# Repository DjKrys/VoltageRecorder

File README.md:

# VoltageRecorder
Celem projektu było zaprojektowanie, montaż i uruchomienie wielokanałowego rejestratora danych do precyzyjnego pomiaru napięcia(The aim of the project was to design, assemble and launch Multi-channel data logger for precise voltage measurement). My engineer's thesis.

# Cel i zakres pracy
Celem pracy jest zaprojektowanie oraz budowa rejestratora do precyzyjnego pomiaru napięcia o zasilaniu bateryjnym. Urządzenie to musi pozwolić na szybką archiwizację danych oraz zapisanie ich w postaci cyfrowej na nieulotną pamięć FLASH. Zbieranie i rejestracja danych na nośnik pamięci o odpowiedniej pojemności pozwala ponadto na prowadzenie wielogodzinnych pomiarów. Aby osiągnąć cel został wykonany schemat elektryczny urządzenia, a następnie na jego podstawie wykonana płytka PCB. Drugim krokiem będzie stworzenie algorytmu w języku C, w celu obsługi podzespołów oraz zarządzania danymi. Zostanie stworzony prosty interfejs użytkownika umożliwiający ustawienie parametrów archiwizacji (ilość próbek na sekundę, zakres pomiarowy), prezentację wyników oraz kalibracje urządzenia.
Ostatnim krokiem była doświadczalna weryfikacja działania układu oraz próba określenia uzyskanych parametrów.

# Założenia
* Urządzenie zasilane z akumulatorka (z pełną jego obsługą, czyli ładowarką + monitoringiem stanu naładowania)
* Pomiary napięcia w ośmiu kanałach analogowych
* Zapis pomiarów do pliku na kartę SD wraz z interwałami czasowymi
* Wyświetlanie informacji na wyświetlaczu
* Projekt płytki PCB oraz montaż 
* Testowe oprogramowanie

# Weryfikacja działania
https://drive.google.com/file/d/1y4KWzrLdbeENvkOfH9YcUIEn7dakh6ji/view?usp=sharing

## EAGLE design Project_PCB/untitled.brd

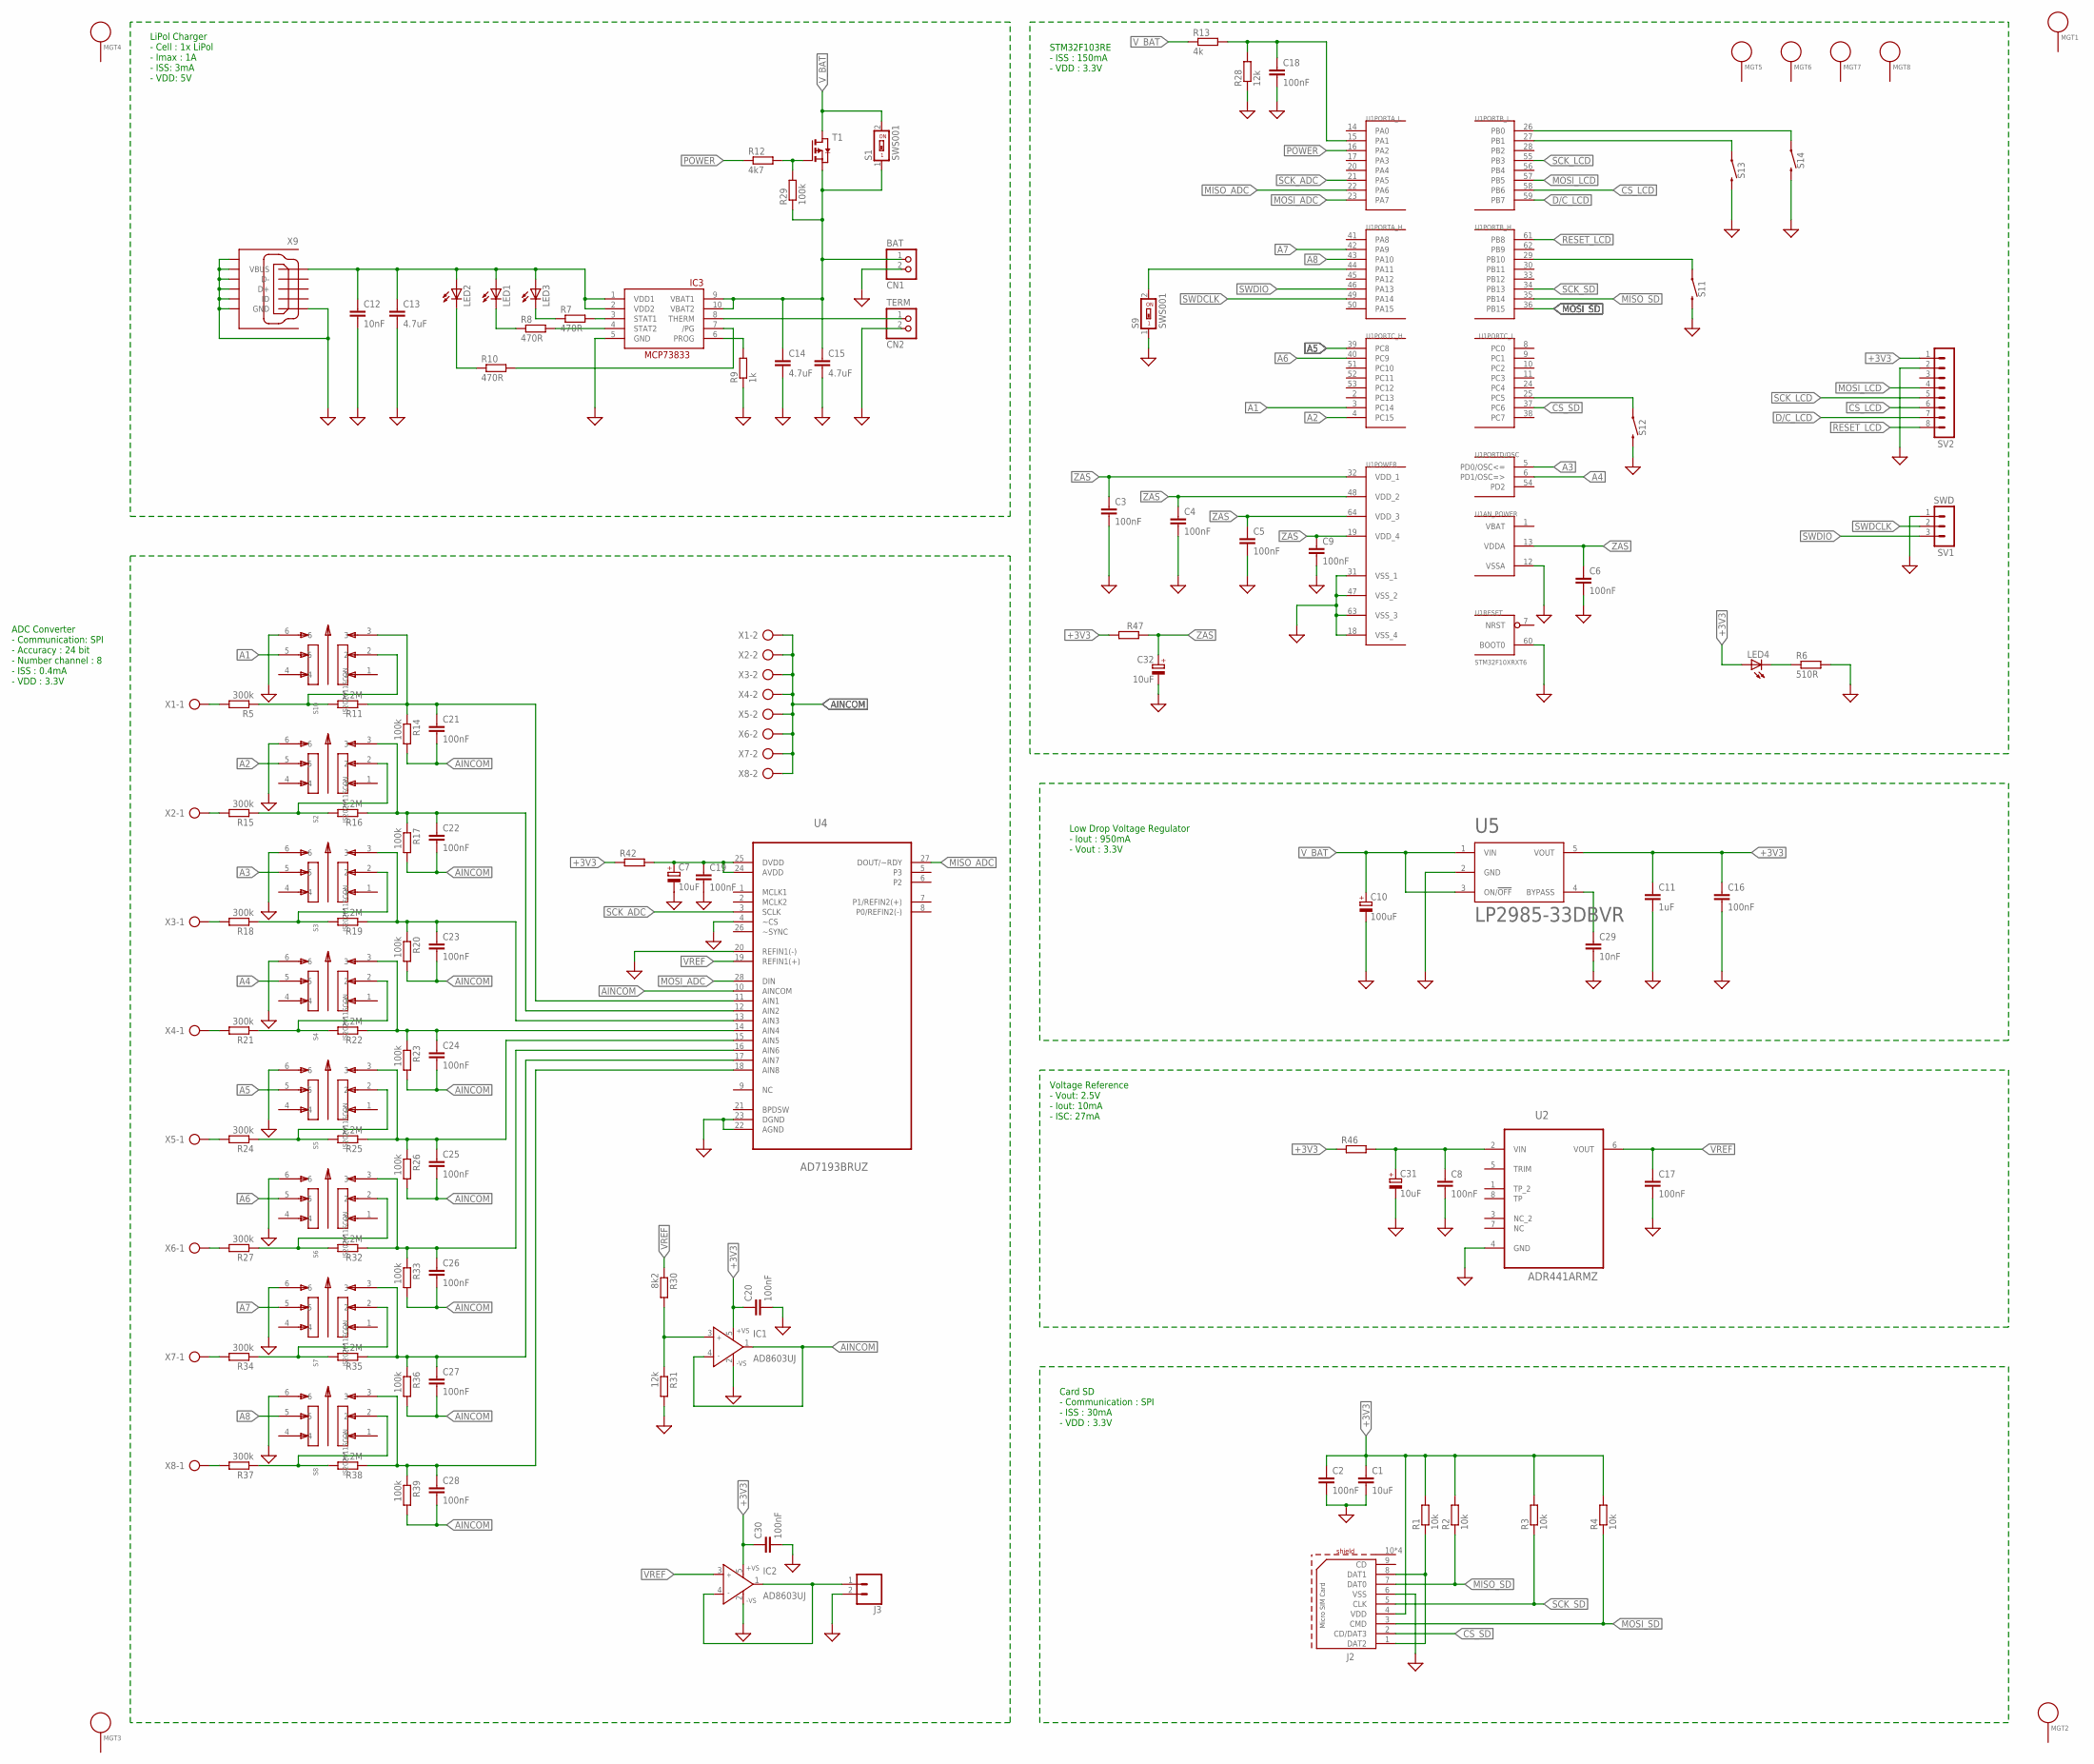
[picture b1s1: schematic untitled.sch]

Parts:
C1: 10uF; C0805
C2, C3, C4, C5, C6, C8, C9, C16, C17, C18, C19, C20, C21, C22, C23, C24, C25, C26, C27, C28, C30: 100nF; C0805
C7, C31, C32: 10uF; SMC_B
C10: 100uF; SMC_B
C11: 1uF; C0805
C12, C29: 10nF; C0805
C13, C14, C15: 4.7uF; C0805
CN1: BAT; JST-PH-2-THM-RA
CN2: TERM; JST-PH-2-THM-RA
IC1, IC2: AD8603UJ; SOT23-5
IC3: MCP73833-UN; MSOP10
J2: 693071020811
J3: CONN_02PTH3; 1X02_LONGPADS
LED1, LED2, LED3, LED4: LEDCHIP-LED0805; CHIP-LED0805
MGT1, MGT2, MGT3, MGT4, MGT5, MGT6, MGT7, MGT8: MOUNTING_HOLE; BEAGLEBONEBLACK_MOUNTING_HOLE
R1, R2, R3, R4: 10k; R0805
R5, R15, R18, R21, R24, R27, R34, R37: 300k; R0805
R6: 510R; R0805
R7, R8, R10: 470R; R0805
R9: 1k; R0805
R11, R16, R19, R22, R25, R32, R35, R38: 1.2M; R0805
R12: 4k7; R0805
R13: 4k; R0805
R14, R17, R20, R23, R26, R29, R33, R36, R39: 100k; R0805
R28, R31: 12k; R0805
R30: 8k2; R0805
R42, R46, R47: R-EU_R1206; R1206
S1, S9: SWS001; SMS-001
S2, S3, S4, S5, S6, S7, S8, S10: JS202011SCQN; SW_JS202011SCQN
S11, S12, S13, S14: MOMENTARY-SWITCH-SPST-SMD-6.2MM-TALL; TACTILE_SWITCH_SMD_6.2MM_TALL
SV1: SWD; MA03-1
SV2: MA08-1
T1: PMOSSOT223; SOT223
U1: STM32F10XRXT6; TQFP64
U2: ADR441ARMZ; SOP65P490X110-8N
U4: AD7193BRUZ; SOP65P640X120-28N
U5: LP2985-33DBVR; SOT-23-5
X1, X2, X3, X4, X5, X6, X7, X8: AK300/2
X9: GHI-CONNECTORS_10118192-0001LF; GHI-CONNECTORS_10118192-0001LF(MICRO-USB-B-AMPHENOL-FCI)

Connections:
+3V3: C1.1, C2.1, C11.1, C16.1, C20.1, C30.1, IC1.5 (+VS), IC2.5 (+VS), J2.4 (VDD), LED4.A, R1.2, R2.2, R3.2, R4.2, R42.1, R46.1, R47.2, SV2.1, U5.5 (VOUT)
A1: S10.5, U1.3 (PC14)
A2: S2.5, U1.4 (PC15)
A3: S3.5, U1.5 (PD0/OSC<=)
A4: S4.5, U1.6 (PD1/OSC=>)
A5: S5.5, U1.39 (PC8)
A6: S6.5, U1.40 (PC9)
A7: S7.5, U1.42 (PA9)
A8: S8.5, U1.43 (PA10)
AINCOM: C21.2, C22.2, C23.2, C24.2, C25.2, C26.2, C27.2, C28.2, IC1.1 (OUT), IC1.4 (IN-), R14.2, R17.2, R20.2, R23.2, R26.2, R33.2, R36.2, R39.2, U4.10 (AINCOM), X1.2, X2.2, X3.2, X4.2, X5.2, X6.2, X7.2, X8.2
CS_LCD: SV2.6, U1.58 (PB6)
CS_SD: J2.2 (CD/DAT3), U1.37 (PC6)
D/C_LCD: SV2.7, U1.59 (PB7)
GND: C1.2, C2.2, C3.2, C4.2, C5.2, C6.2, C7.-, C8.2, C9.2, C10.-, C11.2, C12.2, C13.2, C14.2, C15.2, C16.2, C17.2, C18.2, C19.2, C20.2, C29.2, C30.2, C31.-, C32.-, CN1.2 (1), CN2.2 (1), IC1.2 (-VS), IC2.2 (-VS), IC3.5 (GND), J2.6 (VSS), J3.2, R6.2, R9.1, R28.1, R31.2, S2.6, S3.6, S4.6, S5.6, S6.6, S7.6, S8.6, S9.1, S10.6, S11.B2 (2), S12.B2 (2), S13.B2 (2), S14.B2 (2), SV1.1, SV2.2, U1.12 (VSSA), U1.18 (VSS_4), U1.31 (VSS_1), U1.47 (VSS_2), U1.60 (BOOT0), U1.63 (VSS_3), U2.4 (GND), U4.4 (~CS), U4.20 (REFIN1(-)), U4.22 (AGND), U4.23 (DGND), U5.2 (GND), X9.CGND1 (SGND1), X9.CGND2 (SGND2), X9.CGND3 (SGND3), X9.CGND4 (SGND4), X9.CGND5 (SGND5), X9.CGND6 (SGND6), X9.GND
MISO_ADC: U1.22 (PA6), U4.27 (DOUT/~RDY)
MISO_SD: J2.7 (DAT0), R2.1, U1.35 (PB14)
MOSI_ADC: U1.23 (PA7), U4.28 (DIN)
MOSI_LCD: SV2.4, U1.57 (PB5)
MOSI_SD: J2.3 (CMD), R4.1, U1.36 (PB15)
unnamed: J2.1 (DAT2), J2.8 (DAT1), R1.1
unnamed: LED4.C, R6.1
unnamed: C22.1, R16.1, R17.1, S2.3, U4.12 (AIN2)
unnamed: R5.2, X1.1
unnamed: IC3.3 (STAT1), R7.2
unnamed: IC3.6 (PROG), R9.2
unnamed: IC3.7 (/PG), R10.2
unnamed: LED3.C, R7.1
unnamed: LED1.C, R8.1
unnamed: IC3.4 (STAT2), R8.2
unnamed: LED2.C, R10.1
unnamed: CN2.1 (2), IC3.8 (THERM)
unnamed: C12.1, C13.1, IC3.1 (VDD1), IC3.2 (VDD2), LED1.A, LED2.A, LED3.A, X9.VBUS
unnamed: C21.1, R11.1, R14.1, S10.3, U4.11 (AIN1)
unnamed: R15.1, R16.2, S2.2
unnamed: C29.1, U5.4 (BYPASS)
unnamed: R5.1, R11.2, S10.2
unnamed: R21.1, R22.2, S4.2
unnamed: C26.1, R32.1, R33.1, S6.3, U4.16 (AIN6)
unnamed: C27.1, R35.1, R36.1, S7.3, U4.17 (AIN7)
unnamed: R15.2, X2.1
unnamed: C18.1, R13.2, R28.2, U1.15 (PA1)
unnamed: C23.1, R19.1, R20.1, S3.3, U4.13 (AIN3)
unnamed: IC2.1 (OUT), IC2.4 (IN-), J3.1
unnamed: C7.+, C19.1, R42.2, U4.24 (AVDD), U4.25 (DVDD)
unnamed: R18.2, X3.1
unnamed: C14.1, C15.1, CN1.1 (2), IC3.9 (VBAT1), IC3.10 (VBAT2), R29.1, S1.1, T1.3 (S)
unnamed: R18.1, R19.2, S3.2
unnamed: IC1.3 (IN+), R30.2, R31.1
unnamed: S11.A2 (1), U1.29 (PB10)
unnamed: C24.1, R22.1, R23.1, S4.3, U4.14 (AIN4)
unnamed: C25.1, R25.1, R26.1, S5.3, U4.15 (AIN5)
unnamed: R21.2, X4.1
unnamed: S14.A2 (1), U1.26 (PB0)
unnamed: R24.2, X5.1
unnamed: R24.1, R25.2, S5.2
unnamed: S13.A2 (1), U1.27 (PB1)
unnamed: R12.2, R29.2, T1.1 (G)
unnamed: S9.2, U1.44 (PA11)
unnamed: R27.2, X6.1
unnamed: R27.1, R32.2, S6.2
unnamed: S12.A2 (1), U1.25 (PC5)
unnamed: R34.2, X7.1
unnamed: R34.1, R35.2, S7.2
unnamed: C28.1, R38.1, R39.1, S8.3, U4.18 (AIN8)
unnamed: R37.2, X8.1
unnamed: R37.1, R38.2, S8.2
unnamed: C8.1, C31.+, R46.2, U2.2 (VIN)
POWER: R12.1, U1.16 (PA2)
RESET_LCD: SV2.8, U1.61 (PB8)
SCK_ADC: U1.21 (PA5), U4.3 (SCLK)
SCK_LCD: SV2.5, U1.55 (PB3)
SCK_SD: J2.5 (CLK), R3.1, U1.34 (PB13)
SWDCLK: SV1.2, U1.49 (PA14)
SWDIO: SV1.3, U1.46 (PA13)
VBAT: U1.1 (VBAT)
VREF: C17.1, IC2.3 (IN+), R30.1, U2.6 (VOUT), U4.19 (REFIN1(+))
V_BAT: C10.+, R13.1, S1.2, T1.2 (D), T1.4 (D), U5.1 (VIN), U5.3 (ON/!OFF!)
ZAS: C3.1, C4.1, C5.1, C6.1, C9.1, C32.+, R47.1, U1.13 (VDDA), U1.19 (VDD_4), U1.32 (VDD_1), U1.48 (VDD_2), U1.64 (VDD_3)

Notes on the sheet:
LiPol Charger - Cell : 1x LiPol - Imax : 1A - ISS: 3mA - VDD: 5V
ADC Converter - Communication: SPI - Accuracy : 24 bit - Number channel : 8 - ISS : 0.4mA - VDD : 3.3V
Card SD - Communication : SPI - ISS : 30mA - VDD : 3.3V
STM32F103RE - ISS : 150mA - VDD : 3.3V
Low Drop Voltage Regulator - Iout : 950mA - Vout : 3.3V
Voltage Reference - Vout: 2.5V - Iout: 10mA - ISC: 27mA

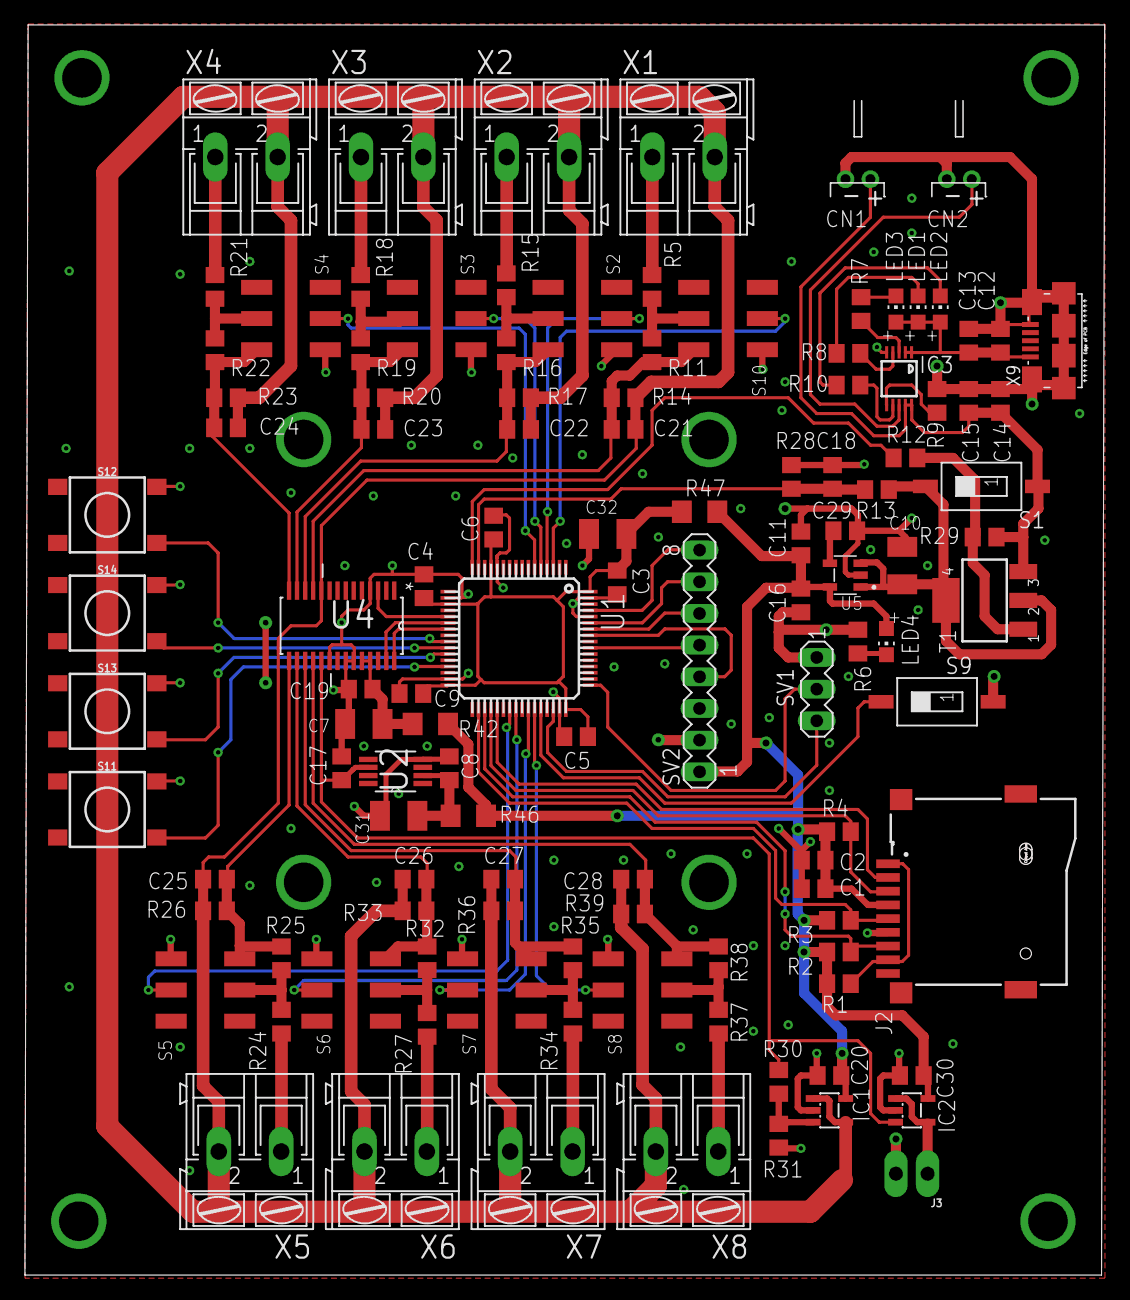
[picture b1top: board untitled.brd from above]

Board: 2 copper layers, 86.6 x 100.3 mm, 123 parts (0 on the bottom side), 77 nets.

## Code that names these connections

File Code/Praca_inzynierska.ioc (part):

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Mcu.Name=STM32F103R(C-D-E)Tx
Mcu.Package=LQFP64
Mcu.UserName=STM32F103RETx
PA1.Signal=ADCx_IN1
PA10.GPIOParameters=GPIO_PuPd,GPIO_Label
PA10.GPIO_Label=A8
PA10.GPIO_PuPd=GPIO_PULLUP
PA10.Signal=GPIO_Input
PA11.GPIOParameters=GPIO_PuPd,GPIO_Label
PA11.GPIO_Label=REC
PA11.GPIO_PuPd=GPIO_PULLUP
PA11.Signal=GPIO_Input
PA13.Signal=SYS_JTMS-SWDIO
PA14.Signal=SYS_JTCK-SWCLK
PA2.GPIOParameters=GPIO_Speed,GPIO_PuPd,GPIO_Label
PA2.GPIO_Label=POWER
PA2.GPIO_PuPd=GPIO_PULLUP
PA2.GPIO_Speed=GPIO_SPEED_FREQ_MEDIUM
PA2.Signal=GPIO_Output
PA5.Mode=Full_Duplex_Master
PA5.Signal=SPI1_SCK
PA6.Mode=Full_Duplex_Master
PA6.Signal=SPI1_MISO
PA7.Mode=Full_Duplex_Master
PA7.Signal=SPI1_MOSI
PA9.GPIOParameters=GPIO_PuPd,GPIO_Label
PA9.GPIO_Label=A7
PA9.GPIO_PuPd=GPIO_PULLUP
PA9.Signal=GPIO_Input
PB0.GPIOParameters=GPIO_PuPd,GPIO_Label
PB0.GPIO_Label=B2
PB0.GPIO_PuPd=GPIO_PULLUP
PB0.Signal=GPIO_Input
PB1.GPIOParameters=GPIO_PuPd,GPIO_Label
PB1.GPIO_Label=B3
PB1.GPIO_PuPd=GPIO_PULLUP
PB1.Signal=GPIO_Input
PB10.GPIOParameters=GPIO_PuPd
PB10.GPIO_PuPd=GPIO_PULLUP
PB10.Signal=GPIO_Input
PB13.Mode=Full_Duplex_Master
PB13.Signal=SPI2_SCK
PB14.Mode=Full_Duplex_Master
PB14.Signal=SPI2_MISO
PB15.Mode=Full_Duplex_Master
PB15.Signal=SPI2_MOSI
PB2.GPIOParameters=GPIO_PuPd,GPIO_Label
PB2.GPIO_Label=B4
PB2.GPIO_PuPd=GPIO_PULLUP
PB2.Signal=GPIO_Input
PB3.Mode=TX_Only_Simplex_Unidirect_Master
PB3.Signal=SPI3_SCK
PB5.Mode=TX_Only_Simplex_Unidirect_Master
PB5.Signal=SPI3_MOSI
PB6.GPIOParameters=GPIO_Speed,PinState,GPIO_Label
PB6.GPIO_Label=CS_LCD
PB6.GPIO_Speed=GPIO_SPEED_FREQ_MEDIUM
PB6.PinState=GPIO_PIN_SET
PB6.Signal=GPIO_Output
PB7.GPIOParameters=GPIO_Speed,GPIO_Label
PB7.GPIO_Label=D/C_LCD
PB7.GPIO_Speed=GPIO_SPEED_FREQ_MEDIUM
PB7.Signal=GPIO_Output
PB8.GPIOParameters=GPIO_Speed,GPIO_Label
PB8.GPIO_Label=RESET_LCD
PB8.GPIO_Speed=GPIO_SPEED_FREQ_MEDIUM
PB8.Signal=GPIO_Output
PC14-OSC32_IN.GPIOParameters=GPIO_PuPd,GPIO_Label
PC14-OSC32_IN.GPIO_Label=A1
PC14-OSC32_IN.GPIO_PuPd=GPIO_PULLUP
PC14-OSC32_IN.Signal=GPIO_Input
PC15-OSC32_OUT.GPIOParameters=GPIO_PuPd,GPIO_Label
PC15-OSC32_OUT.GPIO_Label=A2
PC15-OSC32_OUT.GPIO_PuPd=GPIO_PULLUP
PC15-OSC32_OUT.Signal=GPIO_Input
PC5.GPIOParameters=GPIO_PuPd,GPIO_Label
PC5.GPIO_Label=B1
PC5.GPIO_PuPd=GPIO_PULLUP
PC5.Signal=GPIO_Input
PC6.GPIOParameters=GPIO_Speed,PinState,GPIO_Label
PC6.GPIO_Label=CS_SD
PC6.GPIO_Speed=GPIO_SPEED_FREQ_MEDIUM
PC6.PinState=GPIO_PIN_SET
PC6.Signal=GPIO_Output
PC8.GPIOParameters=GPIO_PuPd,GPIO_Label
PC8.GPIO_Label=A5
PC8.GPIO_PuPd=GPIO_PULLUP
PC8.Signal=GPIO_Input
PC9.GPIOParameters=GPIO_PuPd,GPIO_Label
PC9.GPIO_Label=A6
PC9.GPIO_PuPd=GPIO_PULLUP
PC9.Signal=GPIO_Input
PD0-OSC_IN.GPIOParameters=GPIO_PuPd,GPIO_Label
PD0-OSC_IN.GPIO_Label=A3
PD0-OSC_IN.GPIO_PuPd=GPIO_PULLUP
PD0-OSC_IN.Signal=GPIO_Input
PD1-OSC_OUT.GPIOParameters=GPIO_PuPd,GPIO_Label
PD1-OSC_OUT.GPIO_Label=A4
PD1-OSC_OUT.GPIO_PuPd=GPIO_PULLUP
PD1-OSC_OUT.Signal=GPIO_Input
RCC.SYSCLKFreq_VALUE=64000000
RCC.SYSCLKSource=RCC_SYSCLKSOURCE_PLLCLK
board=custom

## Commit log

2021-02-18 Add code
2021-02-18 Add schematic and project PCB
2021-02-18 Add descritpion device
2021-02-18 Add img and update readme

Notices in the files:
parts and their libraries:
Wurth_Connectors_WR-CRD: Copyright: Würth Elektronik
SparkFun-Connectors: Licensing: Creative Commons ShareAlike 4.0 International - https://creativecommons.org/licenses/by-sa/4.0
